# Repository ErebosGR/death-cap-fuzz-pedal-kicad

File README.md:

View this project on [CADLAB.io](https://cadlab.io/project/25439). 

# Death Cap Fuzz pedal KiCad project
 This is the KiCad project for the PedalPCB Death Cap, a fuzz guitar pedal based on the Fuzzhugger Doom Bloom.

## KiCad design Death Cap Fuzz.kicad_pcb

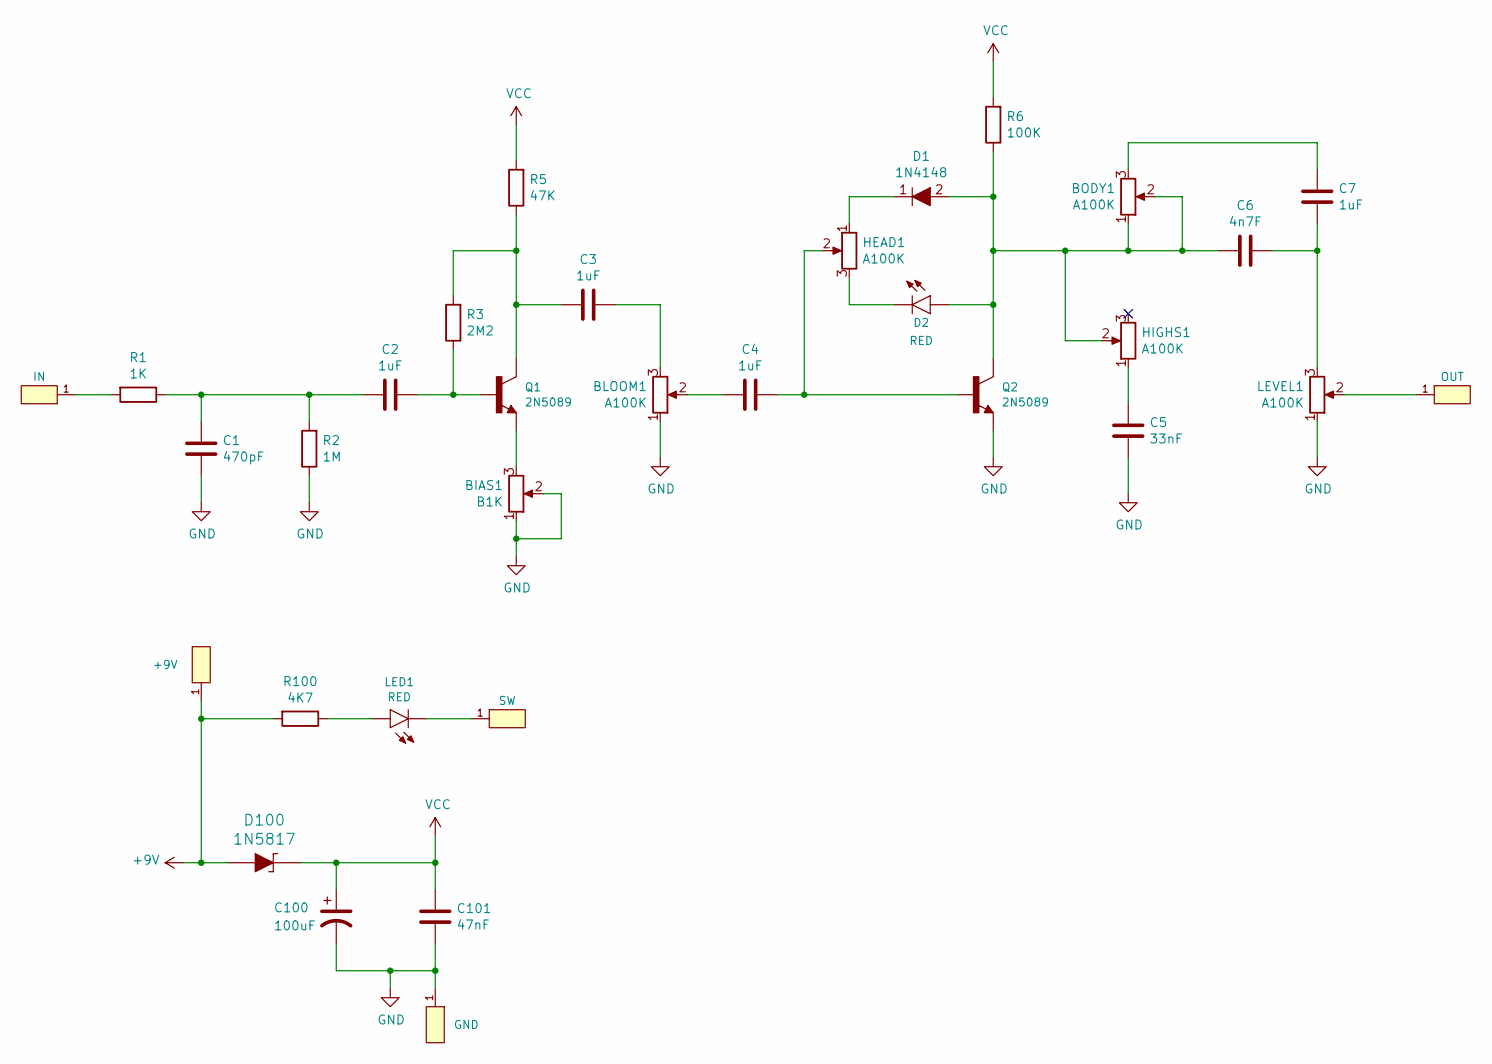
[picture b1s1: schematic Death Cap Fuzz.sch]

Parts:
BIAS1: B1K; Potentiometer_Omeg_PC16BU_Vertical
BLOOM1: A100K; Potentiometer_Omeg_PC16BU_Vertical
BODY1: A100K; Potentiometer_Omeg_PC16BU_Vertical
C1: 470pF; C_Disc_D3.8mm_W2.6mm_P2.50mm
C2, C3, C4, C7: 1uF; C_Rect_L7.2mm_W5.5mm_P5.00mm_FKS2_FKP2_MKS2_MKP2
C5: 33nF; C_Rect_L7.2mm_W2.5mm_P5.00mm_FKS2_FKP2_MKS2_MKP2
C6: 4n7F; C_Rect_L7.2mm_W2.5mm_P5.00mm_FKS2_FKP2_MKS2_MKP2
C100: 100uF; CP_Radial_D6.3mm_P2.50mm
C101: 47nF; C_Rect_L7.2mm_W2.5mm_P5.00mm_FKS2_FKP2_MKS2_MKP2
D1: 1N4148; Diode_DO-35_P10mm; MPN 1N4148; Digi-Key_PN 1N4148FS-ND
D2: RED; LED_3MM
D100: 1N5817; DO-41; MPN 1N5817; Digi-Key_PN 1N5817FSCT-ND
HEAD1: A100K; Potentiometer_Omeg_PC16BU_Vertical
HIGHS1: A100K; Potentiometer_Omeg_PC16BU_Vertical
J1: IN; 1X01_LONGPAD
J2: OUT; 1X01_LONGPAD
J3: +9V; 1X01_LONGPAD
J4: SW; 1X01_LONGPAD
J5: GND; 1X01_LONGPAD
LED1: RED; LED_5MM
LEVEL1: A100K; Potentiometer_Omeg_PC16BU_Vertical
Q1, Q2: 2N5089; TO-92-3
R1: 1K; R_Axial_DIN0207_L6.3mm_D2.5mm_P10.16mm_Horizontal
R2: 1M; R_Axial_DIN0207_L6.3mm_D2.5mm_P15.24mm_Horizontal
R3: 2M2; R_Axial_DIN0207_L6.3mm_D2.5mm_P15.24mm_Horizontal
R5: 47K; R_Axial_DIN0207_L6.3mm_D2.5mm_P10.16mm_Horizontal
R6: 100K; R_Axial_DIN0207_L6.3mm_D2.5mm_P10.16mm_Horizontal
R100: 4K7; R_Axial_DIN0207_L6.3mm_D2.5mm_P10.16mm_Horizontal

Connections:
+9V: D100.A, J3.1, R100.2
GND: BIAS1.1, BIAS1.2, BLOOM1.1, C1.2, C5.1, C100.2, C101.2, J5.1, LEVEL1.1, Q2.1 (E), R2.1
unnamed: BIAS1.3, Q1.1 (E)
unnamed: BLOOM1.2, C4.2
unnamed: BLOOM1.3, C3.1
unnamed: BODY1.1, BODY1.2, C6.1, D1.2, D2.A, HIGHS1.2, Q2.3 (C), R6.1
unnamed: BODY1.3, C7.1
unnamed: C1.1, C2.2, R1.1, R2.2
unnamed: C2.1, Q1.2 (B), R3.1
unnamed: C3.2, Q1.3 (C), R3.2, R5.1
unnamed: C4.1, HEAD1.2, Q2.2 (B)
unnamed: C5.2, HIGHS1.1
unnamed: C6.2, C7.2, LEVEL1.3
unnamed: D1.1, HEAD1.1
unnamed: D2.K (C), HEAD1.3
unnamed: J1.1, R1.2
unnamed: J2.1, LEVEL1.2
unnamed: J4.1, LED1.K (C)
unnamed: LED1.A, R100.1
VCC: C100.1, C101.1, D100.K, R5.2, R6.2

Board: 2 copper layers, 32 parts (0 on the bottom side), 20 nets, no tracks yet.

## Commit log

2022-04-15 Backlink to CADLAB.io has been added.
2022-04-17 Create LICENSE
